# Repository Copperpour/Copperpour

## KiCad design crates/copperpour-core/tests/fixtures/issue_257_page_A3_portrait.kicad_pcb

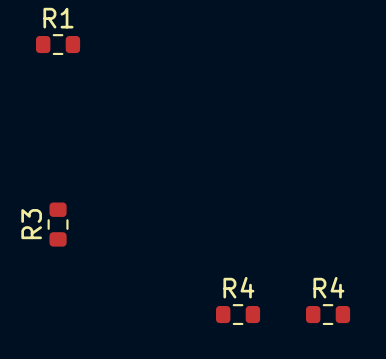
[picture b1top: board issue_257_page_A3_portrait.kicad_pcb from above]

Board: 4 copper layers, 4 parts (0 on the bottom side), 2 nets.

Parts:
R1, R3, R4, R4#2: R_0603_1608Metric

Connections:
NET_G: R4.1, R4#2.1
NET_H: R4.2, R4#2.2
